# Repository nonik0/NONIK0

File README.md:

# Nick's Original Name Indicator Knicknack (version 0)

## Overview

It's a knicknack to indicate your name with the original design by me, Nick. Version 0. NONIK0 for short! The only version there will ever be. I wanted a name badge to wear sometimes and most other times just use for a fancy LED decoration, and also learn some more Rust. Add in a tad of scope creep and you have also have some games, beeps, and other extras, too. For more detail, I have a [project writeup](https://altonimb.us/nonik0/) where I talk about my process of completing this project start to finish, with more of a focus my experience working with Rust.

### Hardware
The hardware is designed in KiCad 8.0 and all design files are included in the [hardware/kicad8.0](hardware/kicad8.0) directory.

The main hardware components are:
- [HCMS-2914](https://www.broadcom.com/products/leds-and-displays/smart-alphanumeric-displays/serial-interface/hcms-2914) 5x7 dot matrix character display
- [ATtiny1604](https://www.microchip.com/en-us/product/attiny1604) 8-bit MCU
- [CMT-322-65-SMT-TR](https://www.digikey.com/en/products/detail/same-sky-formerly-cui-devices/CMT-322-65-SMT-TR/14682617) Piezo Buzzer 3.2mm x 3.2mm
- 2x [PTS526SMG](https://www.digikey.com/en/products/detail/c-k/PTS526SMG15JSMTR2-LFS/10056629) SPST push buttons

Revision #1:
- Swapped test pads and UPDI pads. The UPDI pads were opposite of the buzzer, which made getting the probe clip to remain clipped over the pads with the buzzer in the way more difficult than it needed to be.
- Added solder jumper to HCMS-291x SEL pin. Can optionally cut jumper to Vcc and solder other side to ground to use external oscillator for display.
- Optimized some routing for power and ground.

Revision #2:
- Fixed I2C pin assignment for external JST-SH connector
- Added piezo driver circuit

### Firmware

The firmware is written in Rust and can be found in the [firmware/rust](firmware/rust) directory. As part of the work, I wrote a new [HCMS-29xx driver](https://github.com/nonik0/hcms-29xx) and forked avr-hal to add a Feather32u4 support, which I used for bootstrapping the HCMS-29xx driver work. There is also an older PlatformIO project targetting the Adafruit Feather in the [firmware/cpp](firmware/cpp) directory.

The firmware is navigated using two buttons. Navigation and control is done with the two push buttons. A short press on the right button is a "next" action and will show the next option in the current context (i.e. the menu or active mode). A short press on the left button depends on the given context, and is either a "previous" action or a "alternate" action. A long press on the right button is an "enter/confirm" action and will enter a mode from the menu or, from within a mode, change the current page or enter a submenu. A long press on the left button will do an "exit" action which exits from a mode to the menu, or exits from a submenu from a mode.

#### Modes

- **Name:** The original inspiration for this project. Displays an 8 character name (or other string). Can enter an edit mode to update the name/value and is persisted in EEPROM.
- **Settings:** Change the current max brightness and max current settings for HCMS-29XX display, in addition to toggling the button tones on or off.
- **Vibes:** Inspired from the prototype's zigzag pattern I used for testing scrolling/smoothness. It reminded me of watching mountains pass by from a train windows, so I added this mode with mountains and clouds with a parallax effect. The speed of the clouds and mountains can be changed with buttons.
- **Sensors:** The first of the scope creep feartures. Uses the ADC and can read various channels includes the internal temperature and references voltage, but primary the external voltage on the external JUST port pins for use as a simple voltmeter. Has a settings page where the various ADC parameter can be alterned, I used this for my own learning and understanding of the ADC parameters when implementing.
- **Random:** A simple mode that has several pages to display random values for use as a decision tool: integer values, dice values, "eight ball" yes/maybe/no values, and random cuisine types.
- **Tunnel** A basic tunnel game where you control a runner that moves up/down with left/right buttons and you try to survive as long as possible as the tunnel shrinks.
- **Traffic** Another basic game where a you control a driver that advances to the right as you avoid other traffic (rectangles) progressing to the left.

## Design Images

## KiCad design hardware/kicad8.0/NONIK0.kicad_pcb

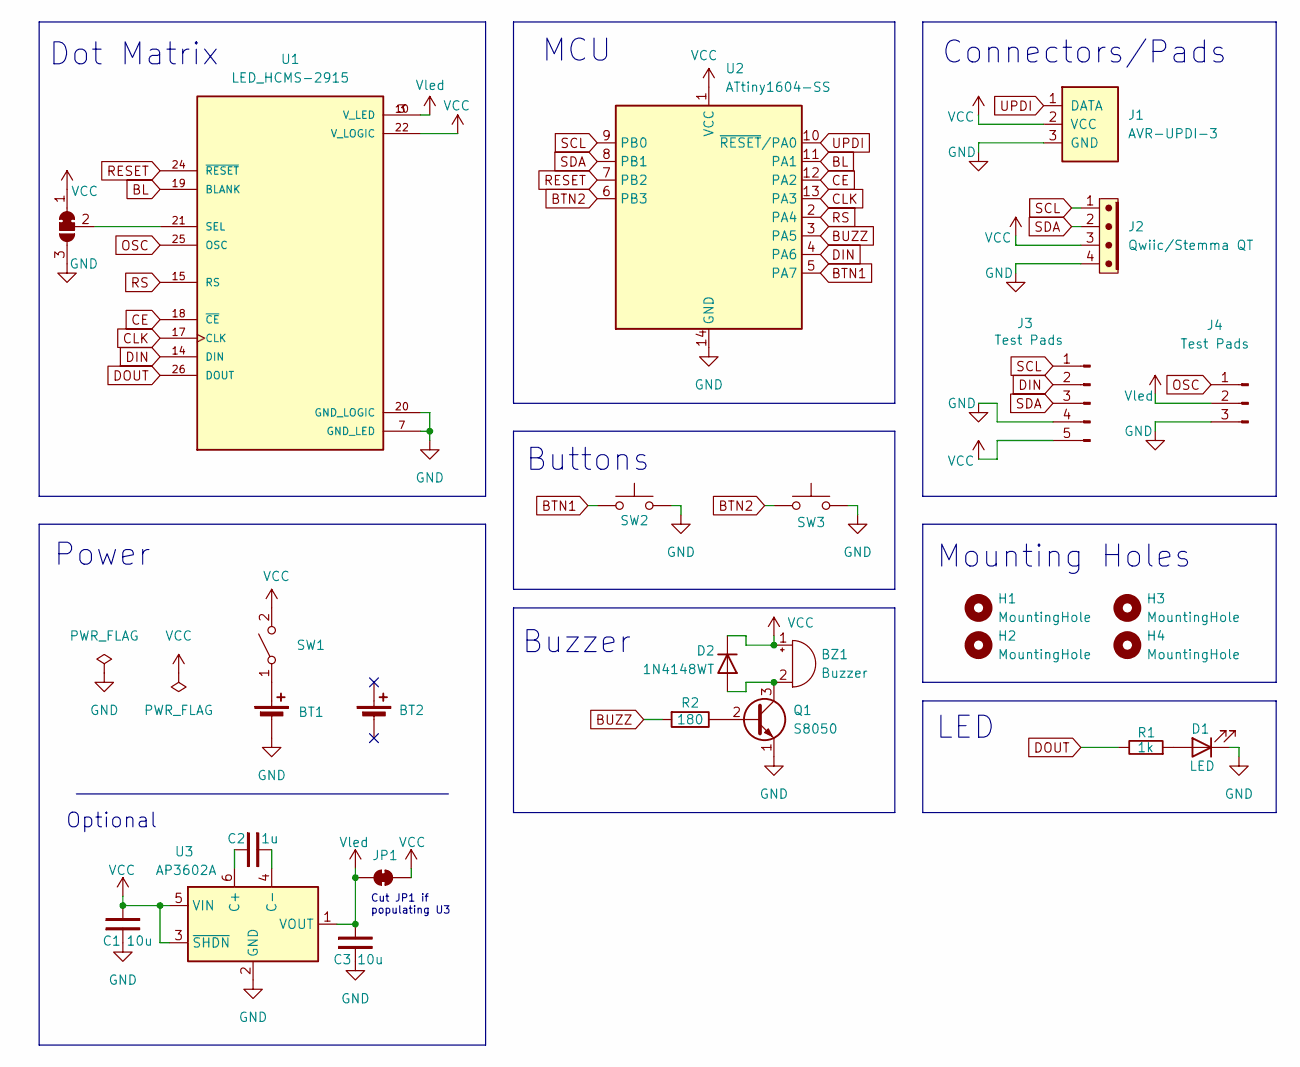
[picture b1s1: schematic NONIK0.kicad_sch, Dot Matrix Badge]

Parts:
BT1: Battery_Cell; BatteryHolder_Keystone_3034_1x20mm
BT2: Battery_Cell; SpareBatteryHolder_Keystone_3034_1x20mm
BZ1: Buzzer; CMT-322-65-SMT-TR
C1, C3: 10u; C_0603_1608Metric
C2: 1u; C_0603_1608Metric
D1: LED; LED_0603_1608Metric
D2: 1N4148WT; D_SOD-523_NoSilkscreen
H1, H2, H3, H4: MountingHole; MountingHole_Custom
J1: AVR-UPDI-3; Pads_1x3_2.54mm
J2: Qwiic/Stemma QT; JST_SH_4P_No Silkscreen
J3: Test Pads; Pads_1x5_1mm
J4: Test Pads; Pads_1x3_2.54mm
JP1: SolderJumper_2_Bridged; SolderJumper_SmallerFootprint
JP2: SolderJumper_3_Bridged12; SolderJumper-3_P1.3mm_Bridged12_RoundedPad1.0x1.5mm
Q1: S8050; SOT-23-SmallerCourtyard
R1: 1k; R_0603_1608Metric
R2: 180; R_0603_1608Metric
SW1: SW_SPST; SW_SPDT_PCM12
SW2, SW3: SW_Push; SW_SPST_PTS526_JLeads
U1: LED_HCMS-2915; HCMS-291X; PARTREV N/A
U2: ATtiny1604-SS; SOIC-14_3.9x8.7mm_P1.27mm
U3: AP3602A; SOT-23-6_SmallerFootprint

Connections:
BL: U1.19 (BLANK), U2.11 (PA1)
BTN1: SW2.1, U2.5 (PA7)
BTN2: SW3.1, U2.6 (PB3)
BUZZ: R2.2, U2.3 (PA5)
CE: U1.18 (~CE), U2.12 (PA2)
CLK: U1.17 (CLK), U2.13 (PA3)
DIN: J3.2, U1.14 (DIN), U2.4 (PA6)
DOUT: R1.2, U1.26 (DOUT)
GND: BT1.2 (-), C1.1, C3.1, D1.1 (K), J1.3 (GND), J2.4, J3.4, J4.3, JP2.3 (B), Q1.1 (E), SW2.2, SW3.2, U1.7 (GND_LED), U1.20 (GND_LOGIC), U2.14 (GND), U3.2 (GND)
unnamed: BT1.1 (+), SW1.1 (A)
unnamed: BZ1.2 (-), D2.2 (A), Q1.3 (C)
unnamed: D1.2 (A), R1.1
unnamed: JP2.2 (C), U1.21 (SEL)
unnamed: Q1.2 (B), R2.1
unnamed: C2.1, U3.6 (C+)
unnamed: C2.2, U3.4 (C-)
OSC: J4.1, U1.25 (OSC)
RESET: U1.24 (~RESET), U2.7 (PB2)
RS: U1.15 (RS), U2.2 (PA4)
SCL: J2.1, J3.1, U2.9 (PB0)
SDA: J2.2, J3.3, U2.8 (PB1)
UPDI: J1.1 (DATA), U2.10 (~RESET/PA0)
VCC: BZ1.1 (+), C1.2, D2.1 (K), J1.2 (VCC), J2.3, J3.5, JP1.2 (B), JP2.1 (A), SW1.2 (B), U1.22 (V_LOGIC), U2.1 (VCC), U3.3 (~SHDN), U3.5 (VIN)
Vled: C3.2, J4.2, JP1.1 (A), U1.3 (V_LED), U1.10 (V_LED), U3.1 (VOUT)

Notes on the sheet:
Cut JP1 if populating U3
Mounting Holes
LED
Optional
MCU
Buttons
Dot Matrix
Connectors/Pads
Power
Buzzer

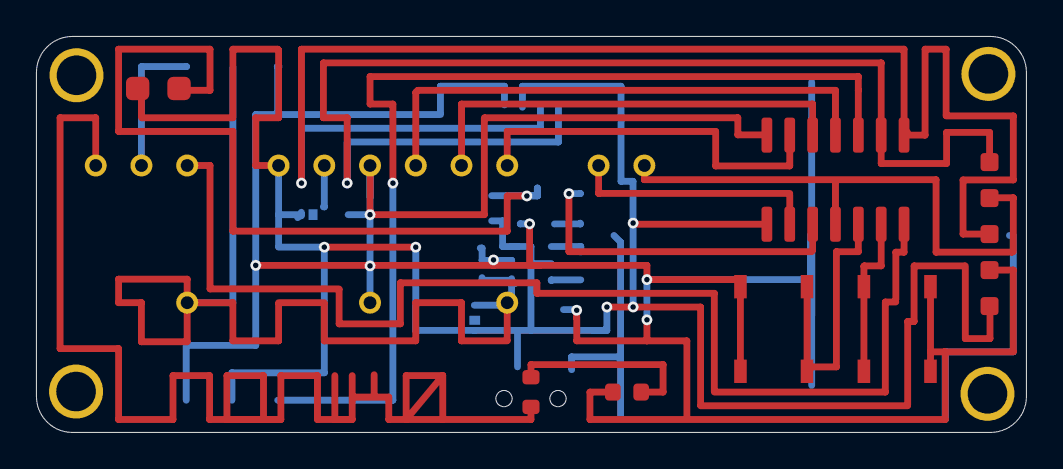
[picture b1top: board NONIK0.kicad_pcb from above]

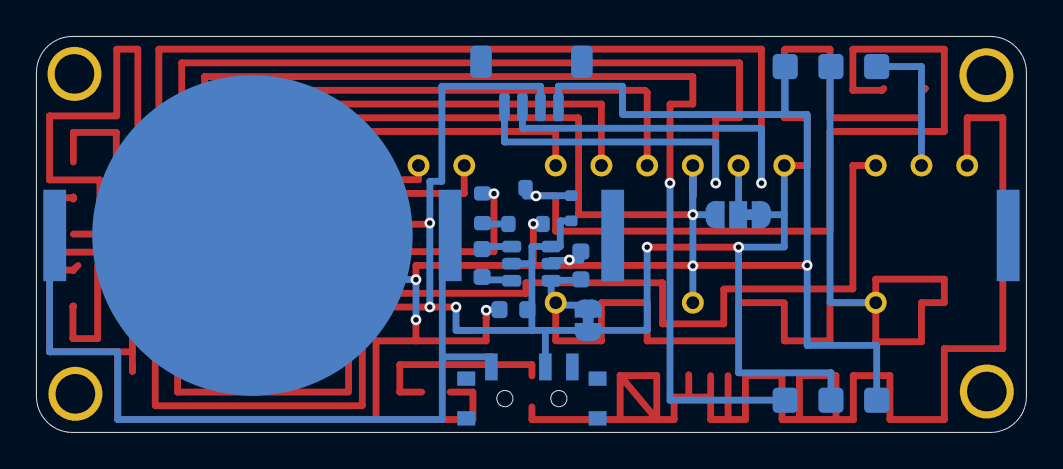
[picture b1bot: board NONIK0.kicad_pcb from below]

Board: 2 copper layers, 55.0 x 22.0 mm, 27 parts (15 on the bottom side), 24 nets.

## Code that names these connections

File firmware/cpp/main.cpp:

#include "HCMS39xx.h"

#define NUM_CHARS 8

#ifdef ARDUINO_ARCH_MEGAAVR
#include <Wire.h>
// static pins:
// SEL: HIGH
#define DIN_PIN PIN_PA6 // 4
#define RS_PIN PIN_PA4  // 2
#define CLK_PIN PIN_PA3 // 13
#define CE_PIN PIN_PA2  // 12
#define BL_PIN PIN_PA1  // 11
#define SEL_PIN HCMS39xx::NO_PIN
// #define RESET_PIN PIN_PB0 // 9
#define RESET_PIN PIN_PB2 // 7

#define BTN1_PIN PIN_PA7 // 5
#define BTN2_PIN PIN_PB3 // 6

#define SDA_PIN PIN_PB1 // 8
// #define SCL_PIN PIN_PB2 // 7
#define SCL_PIN PIN_PB0 // 9

#define BUZZ_PIN PIN_PA5 // 3
#endif

#ifdef ARDUINO_AVR_FEATHER32U4
// static pins:
// 2: OSC: NC
// 8: BLANK: GND
// 10: SEL: HIGH
// 12: Reset: HIGH

// pin mappings feather proto:
// top display
// 7 | CE       | SDA/2
// 8 | BLANK    | SCL/3
// 9 | GND      | 5
// 10| SEL      | 6
// 11| Vlogic   | 9
// 12| Reset    | 10
// bottom display
// 1 | Data Out | SCK
// 2 | OSC      | MOSI
// 3 | Vled     | MISO
// 4 | Data In  | RX/0
// 5 | RS       | TX/1
// 6 | CLK      | GND (have to cut connection and route another pin)
#define DIN_PIN 0
#define RS_PIN 1
#define CLK_PIN 11
#define CE_PIN 2
#define BL_PIN 3
#define SEL_PIN 6
#define RESET_PIN 10

#define DOUT_PIN SCK
#define OSC_PIN MOSI

#define VLOGIC_PIN 9
#define VLED_PIN MISO
#define GND_PIN 5
#endif

#if defined(ARDUINO_ARCH_ESP32)
#define DIN_PIN 35
#define RS_PIN 37
#define CLK_PIN 36
#define CE_PIN 34
#define SEL_PIN HCMS39xx::NO_PIN
// missing pins
#endif

HCMS39xx hcms29xx(NUM_CHARS, DIN_PIN, RS_PIN, CLK_PIN, CE_PIN, BL_PIN, SEL_PIN);
uint8_t brightness = 0x0C;
HCMS39xx::DISPLAY_CURRENT current = HCMS39xx::CURRENT_4_0_mA;

void setup()
{
  Serial.begin(9600);

#if defined(RESET_PIN)
  pinMode(RESET_PIN, OUTPUT);
  digitalWrite(RESET_PIN, HIGH);
#endif

#if defined(ARDUINO_ARCH_MEGAAVR)
  Wire.begin();
  pinMode(BTN1_PIN, INPUT_PULLUP);
  pinMode(BTN2_PIN, INPUT_PULLUP);
#endif

#if defined(ARDUINO_AVR_FEATHER32U4)
  // put into high impedance
  pinMode(DOUT_PIN, INPUT);
  pinMode(OSC_PIN, INPUT);
  pinMode(VLOGIC_PIN, INPUT);
  pinMode(GND_PIN, INPUT);
#endif

  hcms29xx.begin();
  hcms29xx.displayUnblank();
  hcms29xx.setIntOsc();
  hcms29xx.setBrightness(brightness);
  hcms29xx.setCurrent(current);

  hcms29xx.print("I2C Scan");
  delay(1000);
}

uint32_t count1 = 0;
uint32_t count2 = 0;
void loop()
{
#if defined(ARDUINO_ARCH_MEGAAVR)
  /*
  if (digitalRead(BTN1_PIN) == LOW)
  {
    tone(BUZZ_PIN, 4000, 500);
    count1 = 0;

    brightness = (brightness + 1) % 16;
    hcms29xx.setBrightness(brightness);
    char buffer[10];
    snprintf(buffer, sizeof(buffer), "BRIGHT%02d", brightness);
    hcms29xx.print(buffer);
    delay(500);
  }
  if (digitalRead(BTN2_PIN) == LOW)
  {
    tone(BUZZ_PIN, 6000, 500);
    count2 = 0;

    if (current == HCMS39xx::CURRENT_4_0_mA)
    {
      current = HCMS39xx::CURRENT_6_4_mA;
      hcms29xx.print("CUR6.4mA");
    }
    else if (current == HCMS39xx::CURRENT_6_4_mA)
    {
      current = HCMS39xx::CURRENT_9_3_mA;
      hcms29xx.print("CUR9.3mA");
    }
    else if (current == HCMS39xx::CURRENT_9_3_mA)
    {
      current = HCMS39xx::CURRENT_12_8_mA;
      hcms29xx.print("CR12.8mA");
    }
    else if (current == HCMS39xx::CURRENT_12_8_mA)
    {
      current = HCMS39xx::CURRENT_4_0_mA;
      hcms29xx.print("CUR4.0mA");
    }
    hcms29xx.setCurrent(current);
    delay(500);
  }
  */
  hcms29xx.clear();
  hcms29xx.print("Scanning");
  delay(1000);

  for (byte address = 1; address < 127; address++)
  {
    Wire.beginTransmission(address);
    byte error = Wire.endTransmission();

    if (error == 0)
    {
      char buffer[10];
      snprintf(buffer, sizeof(buffer), "ACK:0x%02X", address);
      hcms29xx.clear();
      hcms29xx.print(buffer);
      delay(2000);
    }
  }

#else
  count1 = (count1 + 1) % 10000;

  if (random(0, 2) % 2 == 0)
  {
    count2 = (count2 + 1) % 10000;
  }

  // shift count1 4 decimal places to the left
  uint32_t displayNumber = count1 * 10000 + count2;
  hcms29xx.print(displayNumber);
#endif
  delay(5);
}

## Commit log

2025-01-01 just starting both firmware and hardware
2025-01-21 progress with hcms driver
2025-01-21 cpp firmware, hardware progress
2025-01-22 minor progress
2025-01-22 hcms progress
2025-01-23 starting uno debug
2025-01-23 working driver
2025-01-24 code cleanup
2025-01-24 fancier test output
2025-02-05 almost done with layout
2025-02-06 pcb payout almost complete
2025-02-06 99% done
2025-02-07 halfway through symbol/footprint cleanup
2025-02-07 done with cleanup, making things pretty
2025-02-07 renaming/moving
2025-02-08 images and minor
2025-02-08 buzzer
2025-02-08 minor firmware test
2025-02-09 adding power reg and piezo
2025-02-10 pcb done, pending review
2025-02-10 fit and finish things
2025-02-10 more test pads
2025-02-11 pcb fit and finish
2025-02-20 moving hcms driver to crate dep
2025-02-21 dependency changes
2025-02-24 update hcms
2025-02-24 comment fix
2025-02-27 adding design images
2025-03-01 changing to attiny in progress
2025-03-02 minor
2025-03-06 revert back to proto for now
2025-03-06 parallax animation start
2025-03-07 tweaks to anim
2025-03-07 once_cell impl, unfinished
2025-03-07 random with mutex
2025-03-07 stable for now
2025-03-12 adding 1604 to envs, cleanup
2025-03-12 add features for targets
2025-03-12 working to build for megaxavr
2025-03-13 working attiny panic message
2025-03-13 fixes for animation
2025-03-14 buttons impl, removing feather impl
2025-03-14 menu progress
2025-03-14 working input and modes
2025-03-14 ufmt panic, minimal gains
2025-03-14 improve button func
2025-03-14 cleaner context usage
2025-03-14 settings
2025-03-14 editing name
2025-03-14 cleanup TODO
2025-03-14 starting eeprom
2025-03-15 settings controls update
2025-03-15 eeprom progress, nonfunctional
2025-03-16 eeprom write working with asm
2025-03-17 adding basic adc
2025-03-17 starting utils mode for adc testing
2025-03-17 adjust vibes
2025-03-17 eeprom refactor
2025-03-18 utils progress
2025-03-18 util progress
2025-03-18 utils work
2025-03-18 adc settings ctls untested
2025-03-18 adc settings cleanup
2025-03-18 formatting raw
2025-03-19 adding more config
2025-03-19 temp fix and format improvements
2025-03-19 submenu for adc settings
2025-03-19 minimize display updates
2025-03-19 temp using shared settings
2025-03-19 show fahrenheit
2025-03-19 fix rand
2025-03-19 better than nothing seed value
2025-03-19 renaming stuff, tunnel start
2025-03-19 simple tunnel
2025-03-19 traffic game
2025-03-19 fix gap logic
2025-03-20 adc minor fix
2025-03-20 readme update
2025-03-20 tone impl untested
2025-03-20 pcb revisions
2025-03-20 tone, mildly tested
2025-03-21 random stuff and cleanup
2025-03-21 adjustments
2025-03-21 refactor settings, pt 1
2025-03-22 refactor to save space
2025-03-22 vibe refactor, bug fix
2025-03-24 feather proto basic anim
2025-03-25 adding bjt to drive buzzer
2025-03-27 fit and finish
2025-05-06 absorbing svdrust update from avr-device
2025-05-06 adding features for removing modes, bin got bigger
2025-05-06 tone and debug_panic features
2025-05-06 sensor fixes
2025-05-07 eeprom write working
2025-05-07 avr-hal reverted back to asm impl for eeprom
2025-06-10 no static modes, saves sram and flash, partially complete
2025-06-10 refactor sensor mode into folder
2025-06-10 hacky fix for sensors for now
2025-06-11 refactor ADC and sensors mode
2025-06-11 fix/cleanup
2025-06-11 vref fix
2025-06-12 nametag minor refactor
2025-06-12 improve mode init
2025-06-12 traffic flash optimizations
2025-06-12 settings optimizations
2025-06-21 tone setting
2025-06-22 pcb fixes, in progress
2025-06-22 tone setting fix
2025-06-22 pcb fixes
2025-06-23 adding flyback diode
2025-07-01 kicad 9
2025-07-08 hardware minor
2025-07-22 readme updates
2025-07-22 board rev test
2025-07-22 i2c mode boilerplate
2025-07-22 i2c in progress
2025-07-23 fix board_v0
2025-07-23 working i2c scanner
2025-07-23 boilerplate for second i2c util
2025-07-23 client progress
2025-07-23 host fix
2025-07-23 i2c client untested
2025-07-23 working i2c client
2025-07-24 message client
2025-07-24 i2c testing, chunk issue still
2025-07-29 optimize for no chunking, larger i2c buf
2025-07-29 update images
2025-07-31 new driver version
2025-09-05 reduce buf size
2025-12-11 i2c pin config fixes
2025-12-11 senssor setting change
2025-12-12 fixing lints
2025-12-12 sensors minor fix
2026-04-10 bump crates
2026-04-10 continuity sensor
2026-04-10 dual continuity sensors
2026-04-10 minor code optimization
2026-04-10 support for v0 exp pin
